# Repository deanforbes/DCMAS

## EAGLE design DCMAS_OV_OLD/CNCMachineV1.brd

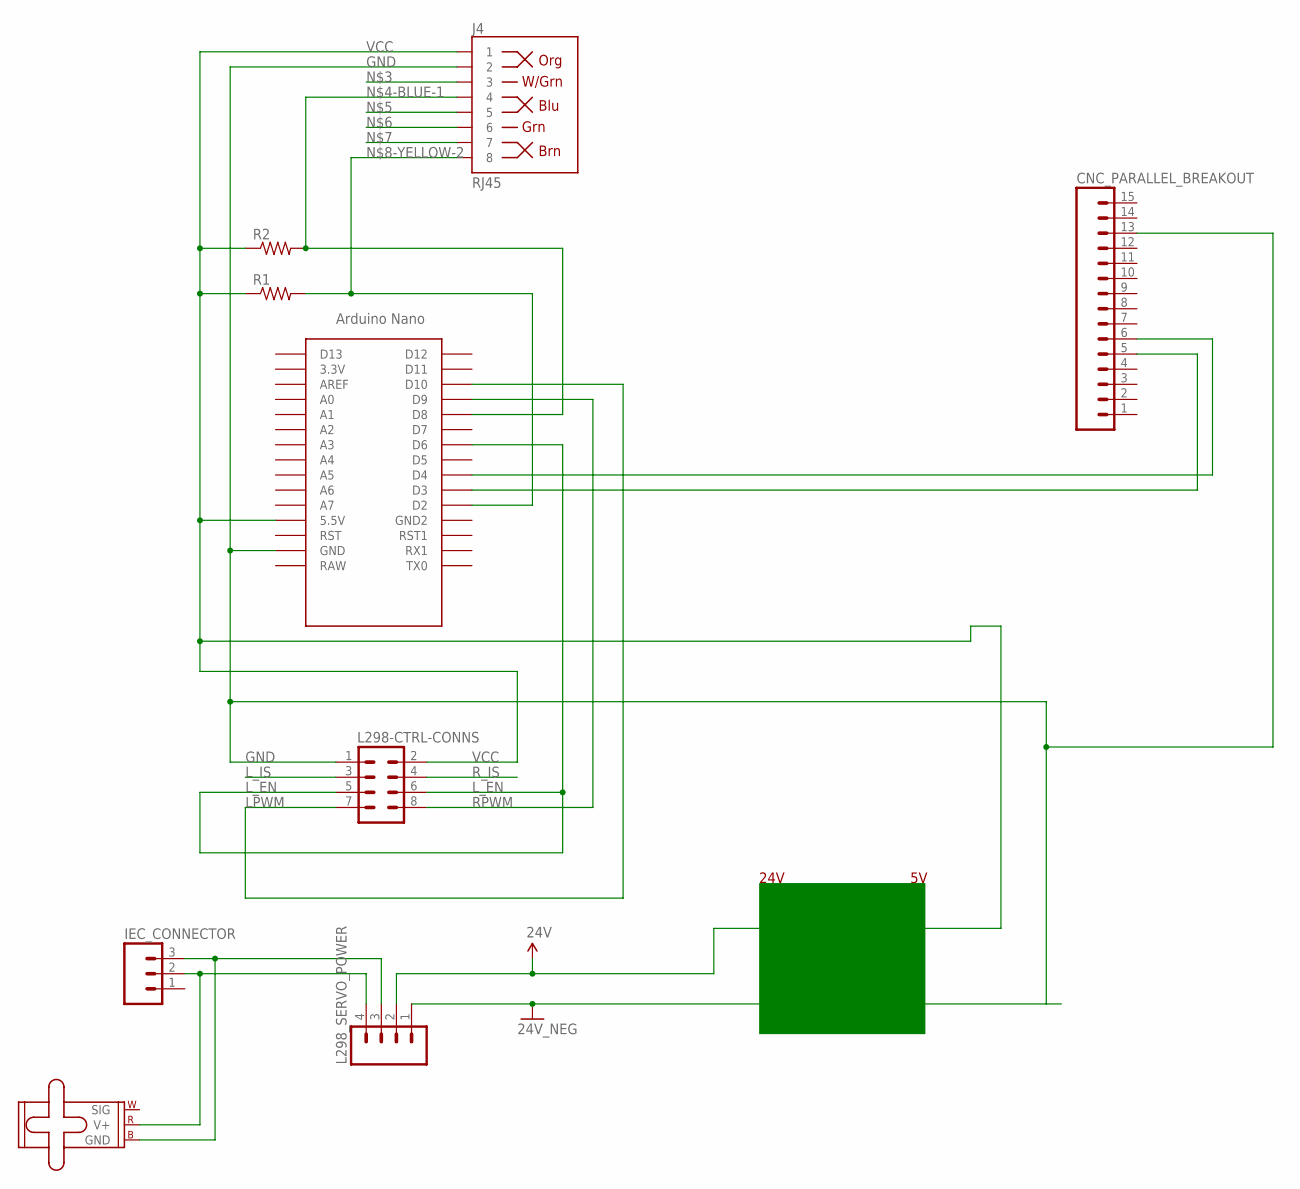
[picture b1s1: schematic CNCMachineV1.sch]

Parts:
CNC_PARALLEL_BREAKOUT: M15; 1X15
IEC_CONNECTOR: M03-SCREW-5MM; SCREWTERMINAL-5MM-3
J4: RJ45; RJ45-8
L298-CTRL-CONNS: M04X2; 2X4
L298_SERVO_POWER: M04SCREW; SCREWTERMINAL-3.5MM-4
M1: SMALL_SERVO; 1X03
R1, R2: RESISTORPTH-1/2W; AXIAL-0.5
U$1: NANO

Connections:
GND: CNC_PARALLEL_BREAKOUT.13, J4.2, L298-CTRL-CONNS.1, L298_SERVO_POWER.1, U$1.GND
LPWM: L298-CTRL-CONNS.7, U$1.D10
L_EN: L298-CTRL-CONNS.5, L298-CTRL-CONNS.6, U$1.D6
L_IS: L298-CTRL-CONNS.3
unnamed: IEC_CONNECTOR.2, L298_SERVO_POWER.4, M1.2 (V+)
unnamed: IEC_CONNECTOR.3, L298_SERVO_POWER.3, M1.3 (GND)
unnamed: CNC_PARALLEL_BREAKOUT.5, U$1.D3
unnamed: J4.4, R2.P$2 (2), U$1.D8
unnamed: CNC_PARALLEL_BREAKOUT.6, U$1.D4
unnamed: J4.8, R1.P$2 (2), U$1.D2
RPWM: L298-CTRL-CONNS.8, U$1.D9
R_IS: L298-CTRL-CONNS.4
VCC: J4.1, L298-CTRL-CONNS.2, L298_SERVO_POWER.2, R1.P$1 (1), R2.P$1 (1), U$1.5V (5.5V)

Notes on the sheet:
24V

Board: 2 copper layers, 9 parts (0 on the bottom side), 11 nets, no tracks yet.

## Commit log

2020-04-02 .
    .

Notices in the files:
parts and their libraries:
SparkFun-Connectors: Licensing: Creative Commons ShareAlike 4.0 International - https://creativecommons.org/licenses/by-sa/4.0
